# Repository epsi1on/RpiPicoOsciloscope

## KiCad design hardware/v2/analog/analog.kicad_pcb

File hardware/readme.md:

3 channel hardware
66mm*112mm 2layer PCB

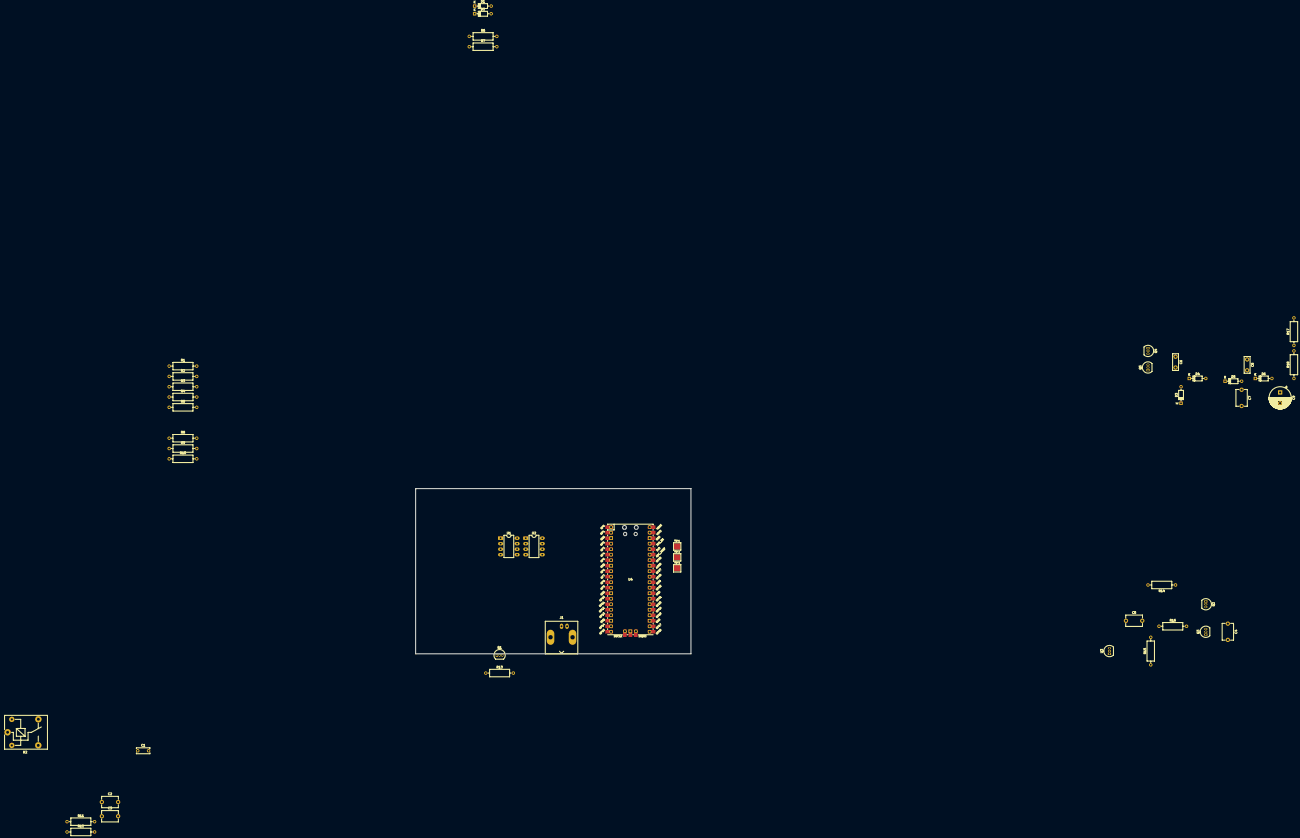
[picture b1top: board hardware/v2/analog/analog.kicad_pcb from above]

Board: 2 copper layers, 127.0 x 76.2 mm, 47 parts (0 on the bottom side), 29 nets, no tracks yet.

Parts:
C1: C; C_Disc_D6.0mm_W2.5mm_P5.00mm
C2: 10pf 1kv; C_Disc_D7.5mm_W5.0mm_P7.50mm
C3: 100pf; C_Disc_D7.5mm_W5.0mm_P7.50mm
C4, C5: 100nF; C_Disc_D7.5mm_W5.0mm_P7.50mm
C6, C8: 100nf; C_Disc_D7.5mm_W2.5mm_P5.00mm
C7: 47uF; C_Disc_D7.5mm_W5.0mm_P7.50mm
C9: 220uF; CP_Radial_D10.0mm_P5.00mm
D1, D2: 1N4148; D_DO-35_SOD27_P7.62mm_Horizontal
D3, D4, D5, D6: 1n4148; D_DO-35_SOD27_P7.62mm_Horizontal
J1: Conn_Coaxial; BNC_Amphenol_B6252HB-NPP3G-50_Horizontal
K2: SANYOU_SRD_Form_C; Relay_SPDT_SANYOU_SRD_Series_Form_C
Q1, Q2, Q4: BC547; TO-92_Inline
Q3, Q5: BC557; TO-92_Inline
R1: 128k; R_Axial_DIN0309_L9.0mm_D3.2mm_P12.70mm_Horizontal
R2: 64k; R_Axial_DIN0309_L9.0mm_D3.2mm_P12.70mm_Horizontal
R3: 32k; R_Axial_DIN0309_L9.0mm_D3.2mm_P12.70mm_Horizontal
R4: 16k; R_Axial_DIN0309_L9.0mm_D3.2mm_P12.70mm_Horizontal
R5: 8k; R_Axial_DIN0309_L9.0mm_D3.2mm_P12.70mm_Horizontal
R6, R7, R17, R18: 10k; R_Axial_DIN0309_L9.0mm_D3.2mm_P12.70mm_Horizontal
R8: 4k; R_Axial_DIN0309_L9.0mm_D3.2mm_P12.70mm_Horizontal
R9: 2k; R_Axial_DIN0309_L9.0mm_D3.2mm_P12.70mm_Horizontal
R10: 1k; R_Axial_DIN0309_L9.0mm_D3.2mm_P12.70mm_Horizontal
R11: 1M; R_Axial_DIN0309_L9.0mm_D3.2mm_P12.70mm_Horizontal
R12: 100K; R_Axial_DIN0309_L9.0mm_D3.2mm_P12.70mm_Horizontal
R13, R14: 1K; R_Axial_DIN0309_L9.0mm_D3.2mm_P12.70mm_Horizontal
R15: 62K; R_Axial_DIN0309_L9.0mm_D3.2mm_P12.70mm_Horizontal
R16: 20K; R_Axial_DIN0309_L9.0mm_D3.2mm_P12.70mm_Horizontal
TP1: 1khz; TestPoint_Pad_3.0x3.0mm
TP2: GNDA; TestPoint_Pad_3.0x3.0mm
TP3: 3v3; TestPoint_Pad_3.0x3.0mm
U1: CD4051B; DIP-8_W7.62mm_LongPads
U2: TL081; DIP-8_W7.62mm_LongPads
U3: TL431LP; TO-92_Inline
U4: Pico; RPi_Pico_SMD_TH

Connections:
+3.3VA: C4.1, D1.1 (K), Q2.3 (E), Q3.3 (E), R6.1, R16.1, TP3.1, U4.35 (ADC_VREF)
+5V: K2.2, Q2.1 (C), Q4.1 (C), R14.2, R17.1, U2.7 (V+), U4.40 (VBUS)
-5V: C9.2, D6.2 (A), R18.2, U1.7 (VEE), U2.4 (V-)
GND: C3.1, C4.2, C7.1, C9.1, D3.1 (K), J1.2 (Ext), Q1.3 (E), Q3.1 (C), Q5.1 (C), R10.2, R12.1, R15.1, U1.6 (INH), U1.8 (VSS), U3.2 (A), U4.3 (GND), U4.8 (GND), U4.13 (GND), U4.18 (GND), U4.23 (GND), U4.28 (GND), U4.38 (GND)
GNDA: D2.2 (A), TP2.1, U4.33 (AGND)
unnamed: C1.1, K2.4
unnamed: C1.2, C2.2, K2.3, R11.2
unnamed: C6.2, D3.2 (A), D4.1 (K)
unnamed: C7.2, D4.2 (A), D5.1 (K)
unnamed: C8.2, D5.2 (A), D6.1 (K)
unnamed: J1.1 (In), K2.1
unnamed: Q1.2 (B), R13.2
unnamed: K2.5, Q1.1 (C)
unnamed: C5.1, Q2.2 (B), Q3.2 (B), R14.1, U3.3 (K)
unnamed: C6.1, C8.1, Q4.3 (E), Q5.3 (E)
unnamed: R1.1, R7.1, U2.6
unnamed: R1.2, R2.1
unnamed: R2.2, R3.1
unnamed: R3.2, R4.1
unnamed: R4.2, R5.1, U1.1 (X4)
unnamed: R5.2, R8.1, U1.5 (X5)
unnamed: R8.2, R9.1, U1.2 (X6)
unnamed: R9.2, R10.1, U1.4 (X7)
unnamed: U1.3 (X), U2.2 (-)
unnamed: C2.1, C3.2, R11.1, R12.2, U2.3 (+)
unnamed: C5.2, R15.2, R16.2, U3.1 (REF)
V_inv_FB: R17.2, R18.1
inv-pwm: Q4.2 (B), Q5.2 (B)
pico-adc: D1.2 (A), D2.1 (K), R6.2, R7.2, U4.31 (GPIO26_ADC0)

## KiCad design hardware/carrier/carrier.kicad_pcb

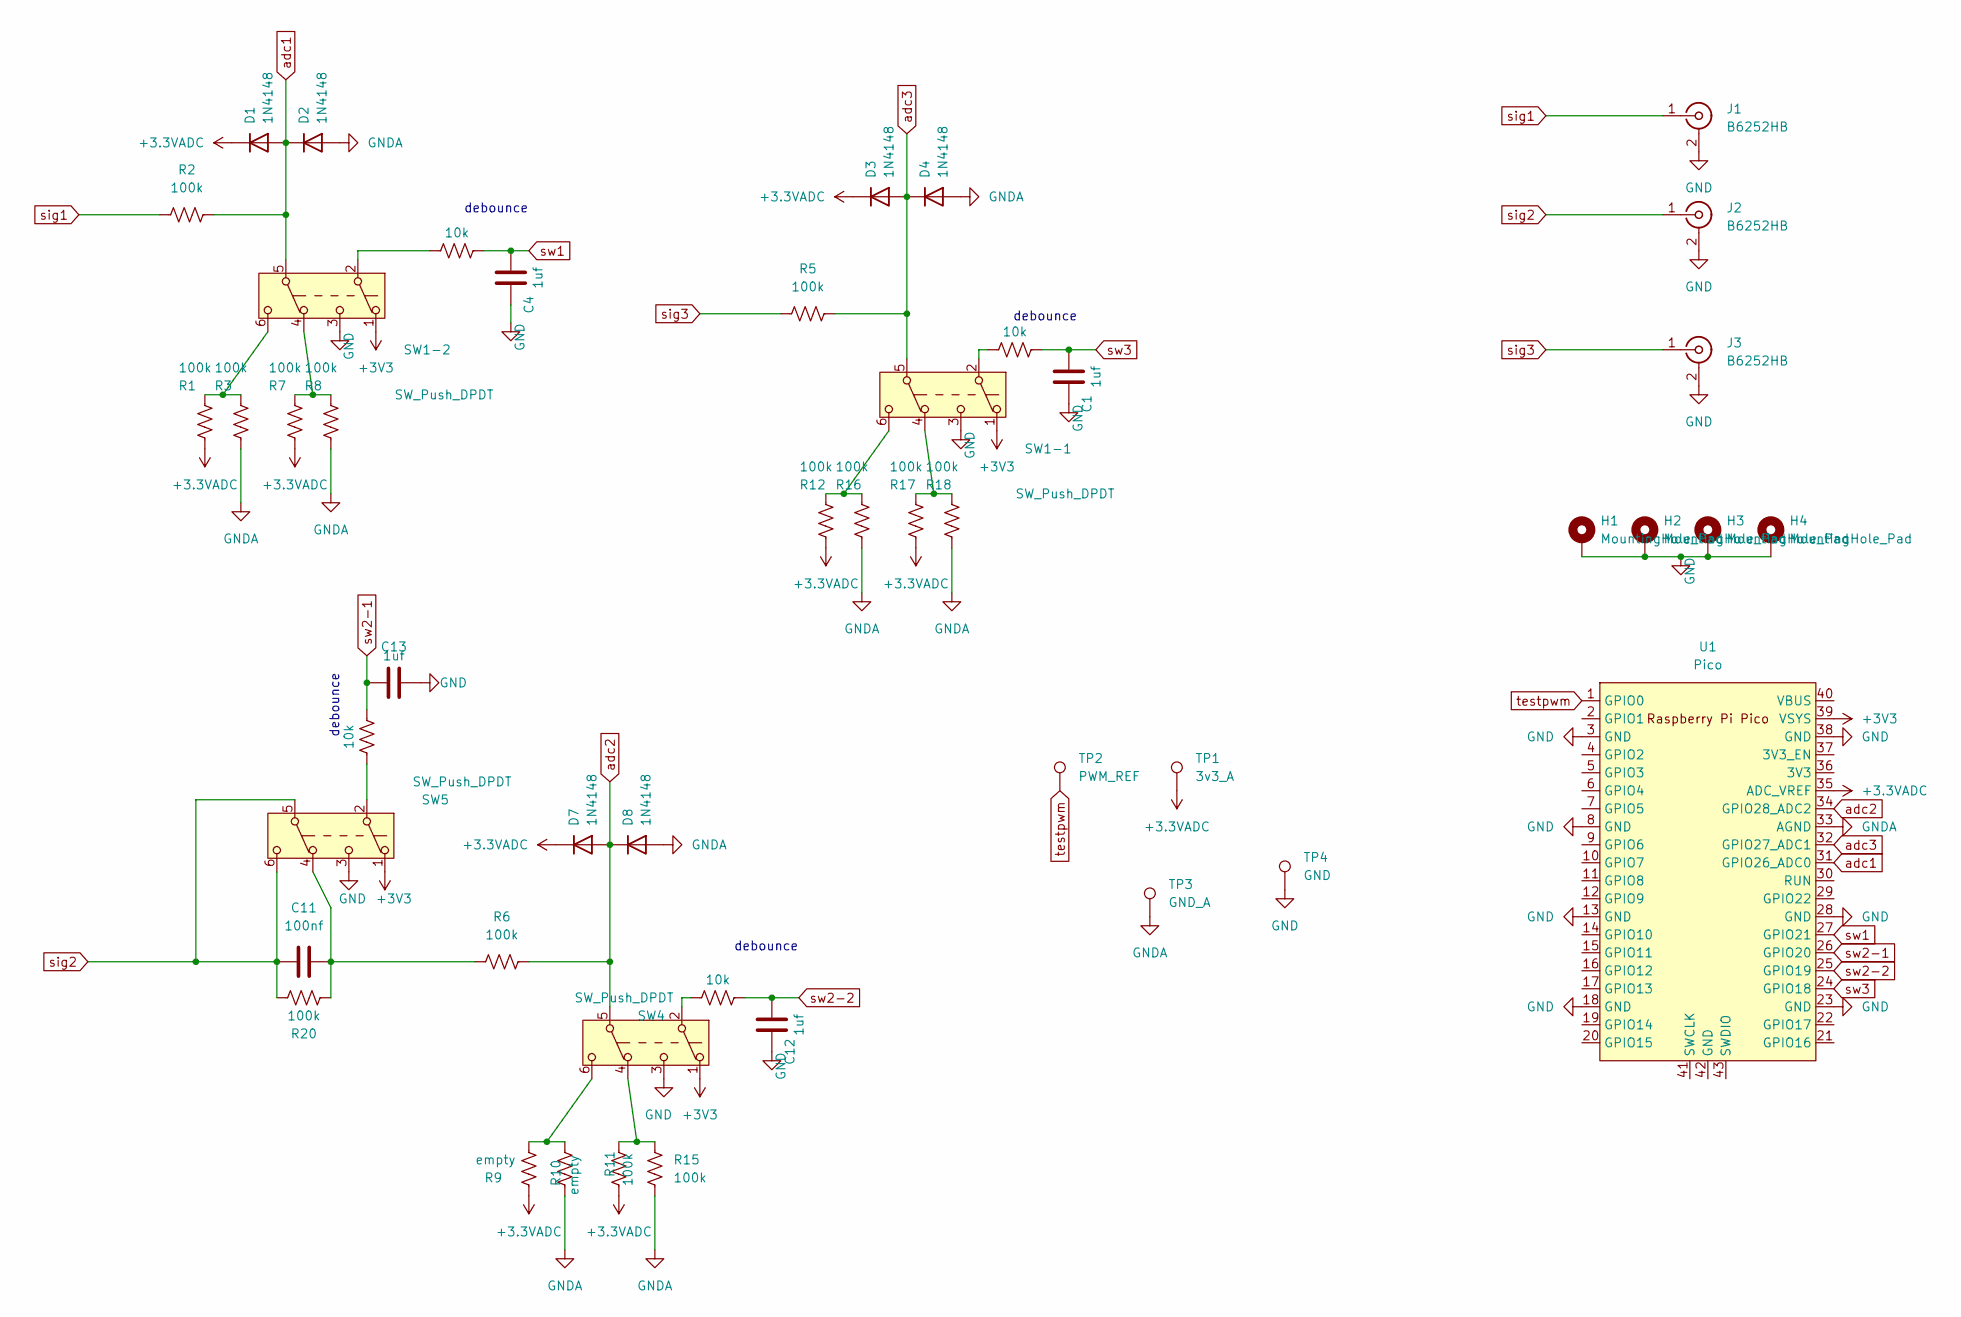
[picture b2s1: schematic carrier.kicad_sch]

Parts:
C1, C4, C12, C13: 1uf; C_Disc_D5.0mm_W2.5mm_P2.50mm
C11: 100nf; C_Disc_D7.5mm_W5.0mm_P7.50mm
D1, D2, D3, D4, D7, D8: 1N4148; D_DO-35_SOD27_P7.62mm_Horizontal
H1, H2, H3, H4: MountingHole_Pad; MountingHole_3mm
J1, J2, J3: B6252HB; BNC_Amphenol_B6252HB-NPP3G-50_Horizontal
R1, R2, R3, R5, R6, R7, R8, R11, R12, R15, R16, R17, R18, R20: 100k; R_Axial_DIN0207_L6.3mm_D2.5mm_P10.16mm_Horizontal
R4, R13, R14, R19: 10k; R_Axial_DIN0207_L6.3mm_D2.5mm_P10.16mm_Horizontal
R9, R10: empty; R_Axial_DIN0207_L6.3mm_D2.5mm_P10.16mm_Horizontal
SW1-1, SW1-2, SW4, SW5: SW_Push_DPDT; button_switch_6mm
TP1: 3v3_A; TestPoint_Pad_D3.0mm
TP2: PWM_REF; TestPoint_Pad_D3.0mm
TP3: GND_A; TestPoint_Pad_D3.0mm
TP4: GND; TestPoint_Pad_D3.0mm
U1: Pico; RPi_Pico_SMD_TH

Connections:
+3.3VADC: D1.1 (K), D3.1 (K), D7.1 (K), R1.2, R7.2, R9.2, R11.2, R12.2, R17.2, TP1.1, U1.35 (ADC_VREF)
+3V3: SW1-1.1 (A), SW1-2.1 (A), SW4.1 (A), SW5.1 (A), U1.39 (VSYS)
GND: C1.1, C4.1, C12.1, C13.1, H1.1, H2.1, H3.1, H4.1, J1.2 (Ext), J2.2 (Ext), J3.2 (Ext), SW1-1.3 (C), SW1-2.3 (C), SW4.3 (C), SW5.3 (C), TP4.1, U1.3 (GND), U1.8 (GND), U1.13 (GND), U1.18 (GND), U1.23 (GND), U1.28 (GND), U1.38 (GND)
GNDA: D2.2 (A), D4.2 (A), D8.2 (A), R3.2, R8.2, R10.2, R15.2, R16.2, R18.2, TP3.1, U1.33 (AGND)
unnamed: C11.2, R6.2, R20.1, SW5.4 (A)
unnamed: R1.1, R3.1, SW1-2.6 (C)
unnamed: R4.2, SW1-2.2 (B)
unnamed: R7.1, R8.1, SW1-2.4 (A)
unnamed: R9.1, R10.1, SW4.6 (C)
unnamed: R11.1, R15.1, SW4.4 (A)
unnamed: R12.1, R16.1, SW1-1.6 (C)
unnamed: R13.2, SW4.2 (B)
unnamed: R14.2, SW5.2 (B)
unnamed: R17.1, R18.1, SW1-1.4 (A)
unnamed: R19.2, SW1-1.2 (B)
adc1: D1.2 (A), D2.1 (K), R2.1, SW1-2.5 (B), U1.31 (GPIO26_ADC0)
adc2: D7.2 (A), D8.1 (K), R6.1, SW4.5 (B), U1.34 (GPIO28_ADC2)
adc3: D3.2 (A), D4.1 (K), R5.1, SW1-1.5 (B), U1.32 (GPIO27_ADC1)
sig1: J1.1 (In), R2.2
sig2: C11.1, J2.1 (In), R20.2, SW5.5 (B), SW5.6 (C)
sig3: J3.1 (In), R5.2
sw1: C4.2, R4.1, U1.27 (GPIO21)
sw2-1: C13.2, R14.1, U1.26 (GPIO20)
sw2-2: C12.2, R13.1, U1.25 (GPIO19)
sw3: C1.2, R19.1, U1.24 (GPIO18)
testpwm: TP2.1, U1.1 (GPIO0)

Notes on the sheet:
debounce

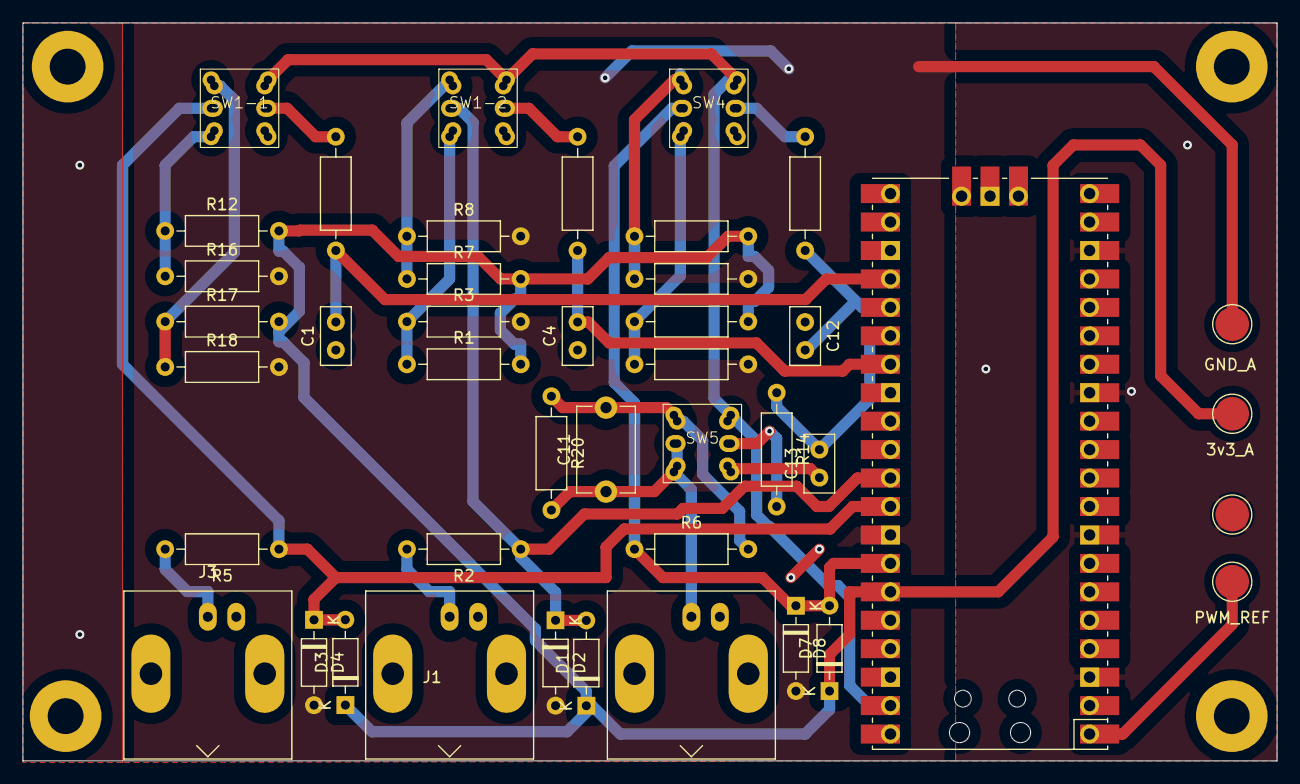
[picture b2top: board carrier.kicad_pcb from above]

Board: 2 copper layers, 112.0 x 65.9 mm, 47 parts (0 on the bottom side), 26 nets.

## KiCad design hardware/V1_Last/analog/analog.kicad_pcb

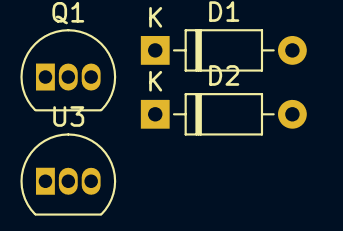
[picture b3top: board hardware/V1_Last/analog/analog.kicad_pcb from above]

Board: 2 copper layers, 4 parts (0 on the bottom side), 2 nets, no tracks yet.

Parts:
D1, D2: 1N4148; D_DO-35_SOD27_P7.62mm_Horizontal
Q1: BC547; TO-92_Inline
U3: TL431LP; TO-92_Inline

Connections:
GND: D2.2 (A), Q1.3 (E)
adc: D1.2 (A), D2.1 (K)

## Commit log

2023-08-01 Add .gitattributes, .gitignore, and README.md.
2023-08-01 Add project files.
2023-10-16 update reamde
2023-11-14 massive update
2024-08-13 POC3
2024-08-13 added kicad
2024-08-13 readme
2024-09-16 update (channel can chenge)
2024-10-26 Analog Part Changes
    EN : Schematic is Modified
    FA : نقشه مدار تغییر یافت
2024-10-30 bugfix - update
2024-11-03 add pdf output
2024-11-04 update 2
2024-11-06 Schematic Changed V2.1.1
    Schematic is Updated to Version 2.1.1
    with Bug fixes
2024-11-06 Correct Bug in V2.1.1
    D2 Anode Pin Corrected
2024-11-09 Create LICENSE
    لایسنس
2024-11-10 schematics & Buffer.BlockCopy replacement - performance improvement
2024-11-11 update - performance improvement
2024-11-11 SharpFftw
2024-11-11 native fftw
